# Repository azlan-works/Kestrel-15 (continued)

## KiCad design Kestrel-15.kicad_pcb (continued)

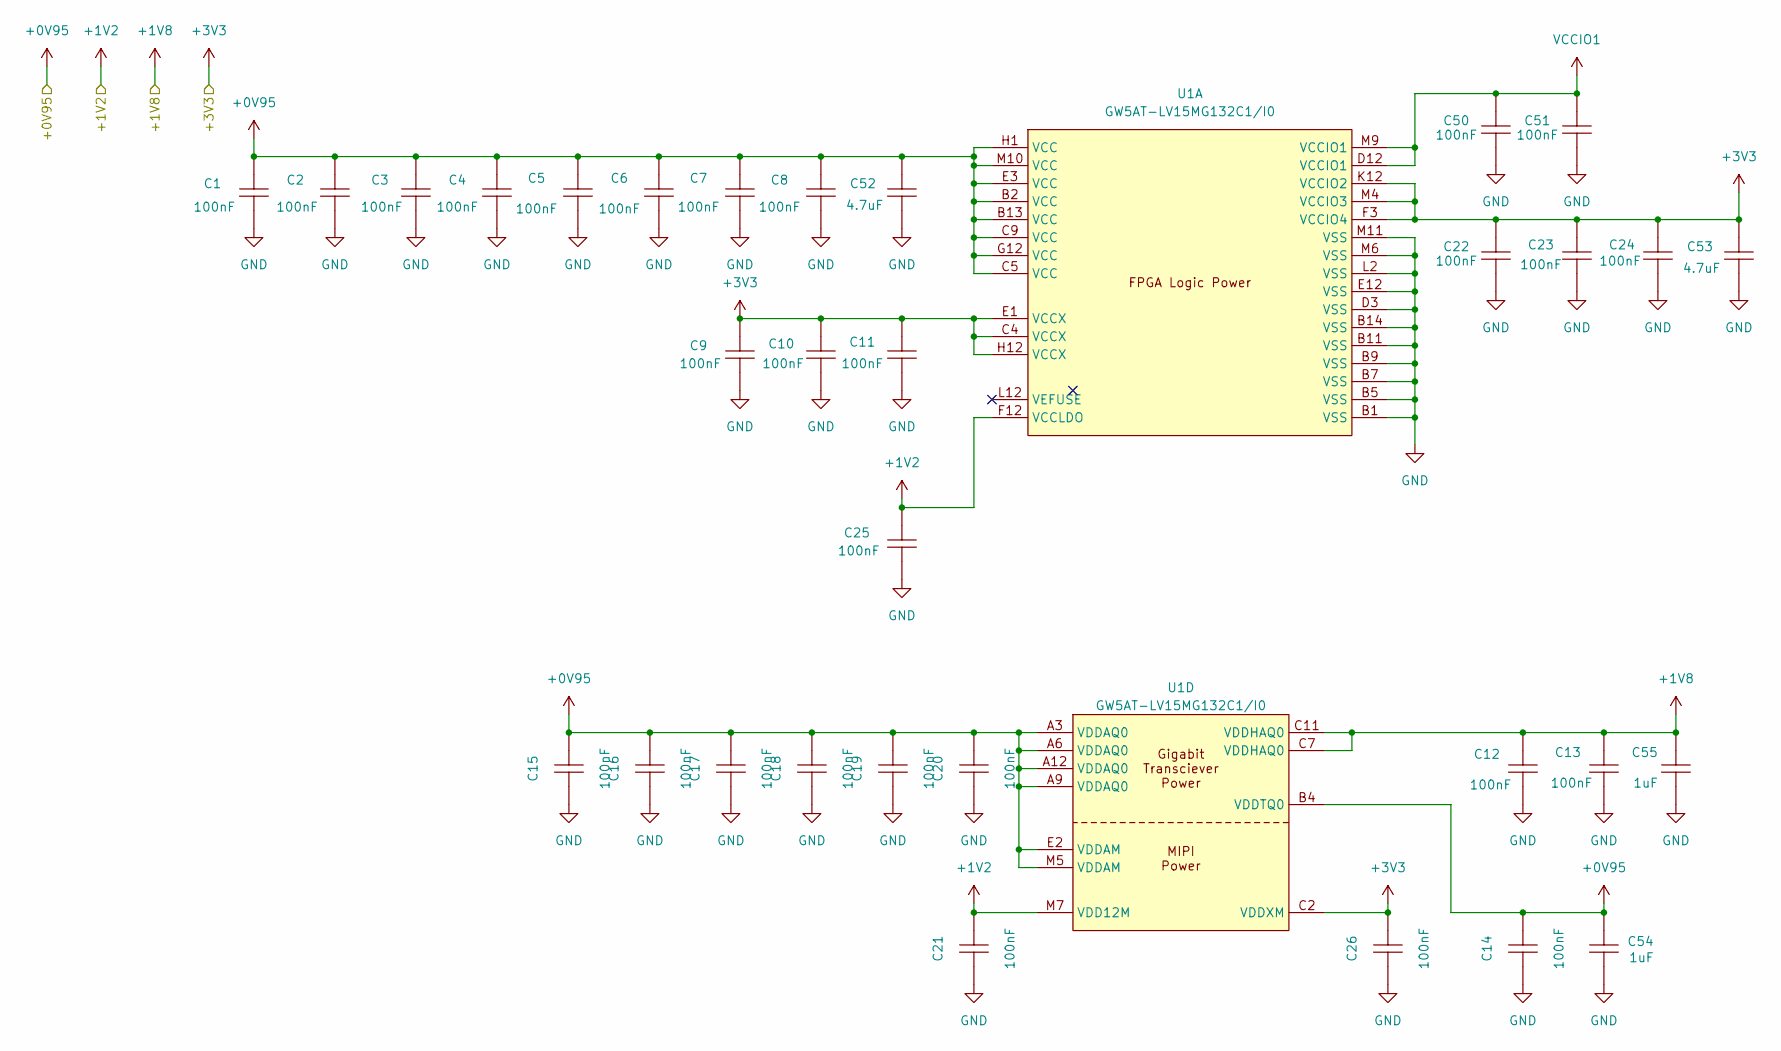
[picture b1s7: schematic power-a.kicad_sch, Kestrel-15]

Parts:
C1, C2, C3, C4, C5, C6, C7, C8, C9, C10, C11, C12, C13, C14, C15, C16, C17, C18, C19, C20, C21, C22, C23, C24, C25, C26, C50, C51: 100nF; C0201; MPN 0201X104M250NT; LCSC Part C52033358
C52, C53: 4.7uF; C0402; MPN CL05A475MP5NRNC; LCSC Part C23733
C54, C55: 1uF; C0402; MPN CL05A105KA5NQNC; LCSC Part C52923
U1: GW5AT-LV15MG132C1/I0; CSBGA-132_L8.0-W8.0-P0.50-TL_GW1N-2K-MG132X1; MPN GW5AT-LV15MG132C1/I0; LCSC Part C54067362

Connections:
+0V95: C1.2, C2.2, C3.2, C4.2, C5.2, C6.2, C7.2, C8.2, C14.2, C15.2, C16.2, C17.2, C18.2, C19.2, C20.2, C52.2, C54.2, U1.A3 (VDDAQ0), U1.A6 (VDDAQ0), U1.A9 (VDDAQ0), U1.A12 (VDDAQ0), U1.B2 (VCC), U1.B4 (VDDTQ0), U1.B13 (VCC), U1.C5 (VCC), U1.C9 (VCC), U1.E2 (VDDAM), U1.E3 (VCC), U1.G12 (VCC), U1.H1 (VCC), U1.M5 (VDDAM), U1.M10 (VCC); also elsewhere on the board
+1V2: C21.2, C25.2, U1.F12 (VCCLDO), U1.M7 (VDD12M); also elsewhere on the board
+1V8: C12.2, C13.2, C55.2, U1.C7 (VDDHAQ0), U1.C11 (VDDHAQ0); also elsewhere on the board
+3V3: C9.2, C10.2, C11.2, C22.2, C23.2, C24.2, C26.2, C53.2, U1.C2 (VDDXM), U1.C4 (VCCX), U1.E1 (VCCX), U1.F3 (VCCIO4), U1.H12 (VCCX), U1.K12 (VCCIO2), U1.M4 (VCCIO3); also elsewhere on the board
GND: C1.1, C2.1, C3.1, C4.1, C5.1, C6.1, C7.1, C8.1, C9.1, C10.1, C11.1, C12.1, C13.1, C14.1, C15.1, C16.1, C17.1, C18.1, C19.1, C20.1, C21.1, C22.1, C23.1, C24.1, C25.1, C26.1, C50.1, C51.1, C52.1, C53.1, C54.1, C55.1, U1.B1 (VSS), U1.B5 (VSS), U1.B7 (VSS), U1.B9 (VSS), U1.B11 (VSS), U1.B14 (VSS), U1.D3 (VSS), U1.E12 (VSS), U1.L2 (VSS), U1.M6 (VSS), U1.M11 (VSS); also elsewhere on the board
VCCIO1: C50.2, C51.2, U1.D12 (VCCIO1), U1.M9 (VCCIO1); also elsewhere on the board

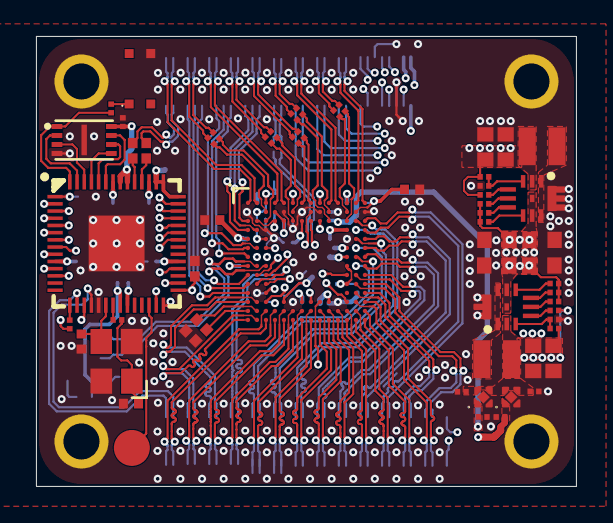
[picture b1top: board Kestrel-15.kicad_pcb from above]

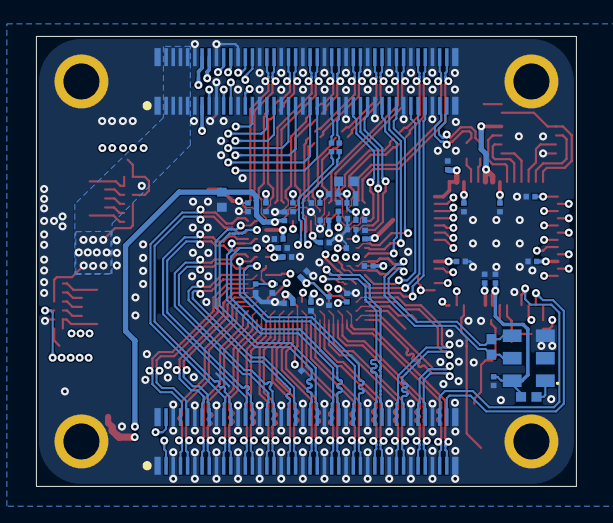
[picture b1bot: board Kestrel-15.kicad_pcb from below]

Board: 6 copper layers, 30.0 x 25.0 mm, 110 parts (46 on the bottom side), 157 nets.
